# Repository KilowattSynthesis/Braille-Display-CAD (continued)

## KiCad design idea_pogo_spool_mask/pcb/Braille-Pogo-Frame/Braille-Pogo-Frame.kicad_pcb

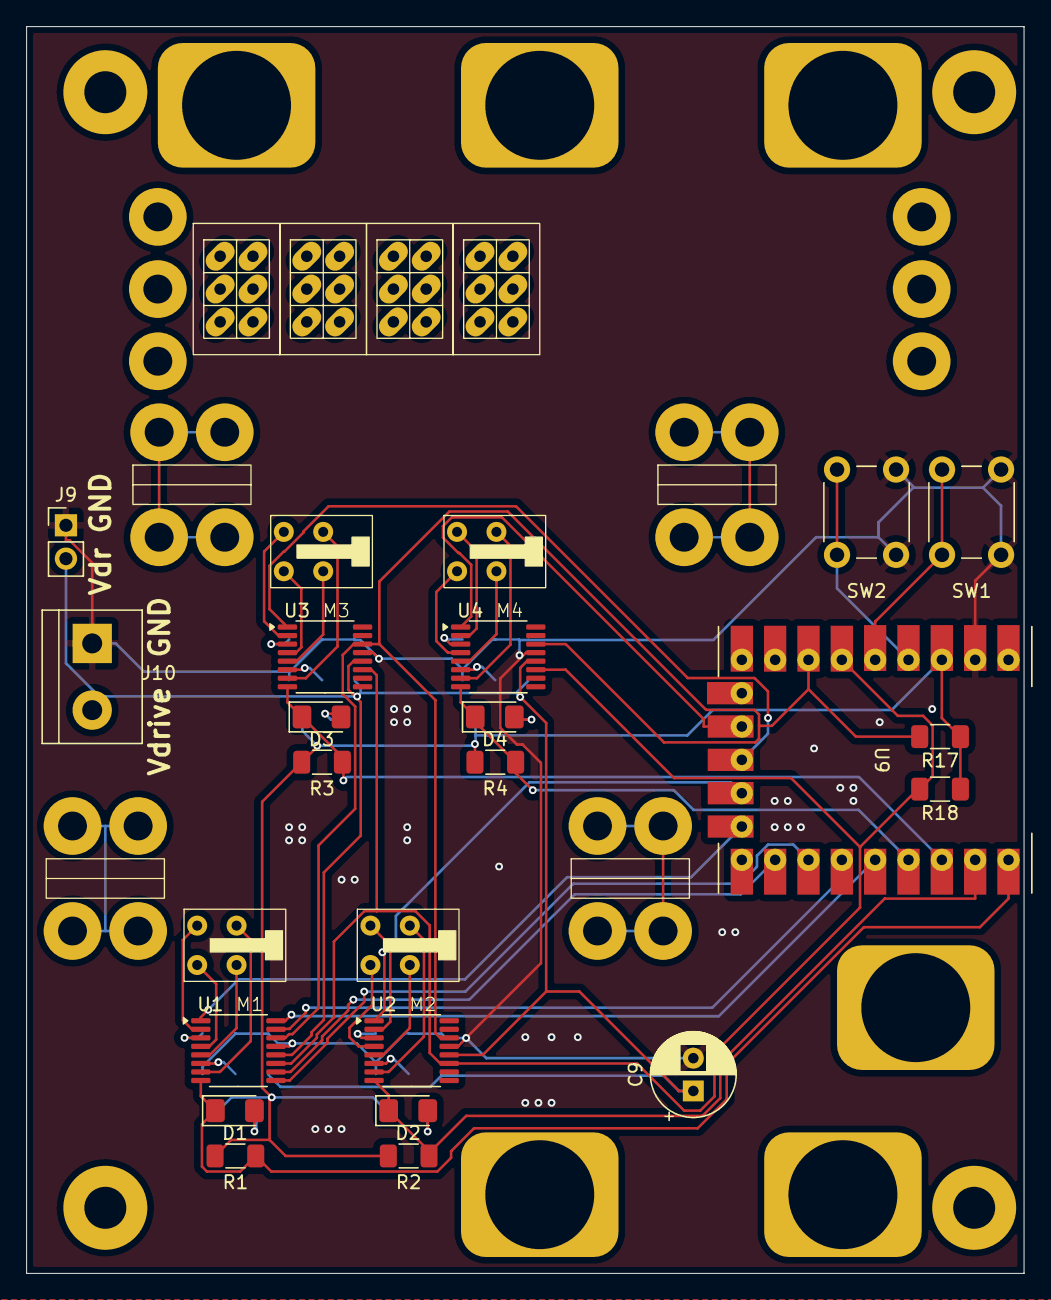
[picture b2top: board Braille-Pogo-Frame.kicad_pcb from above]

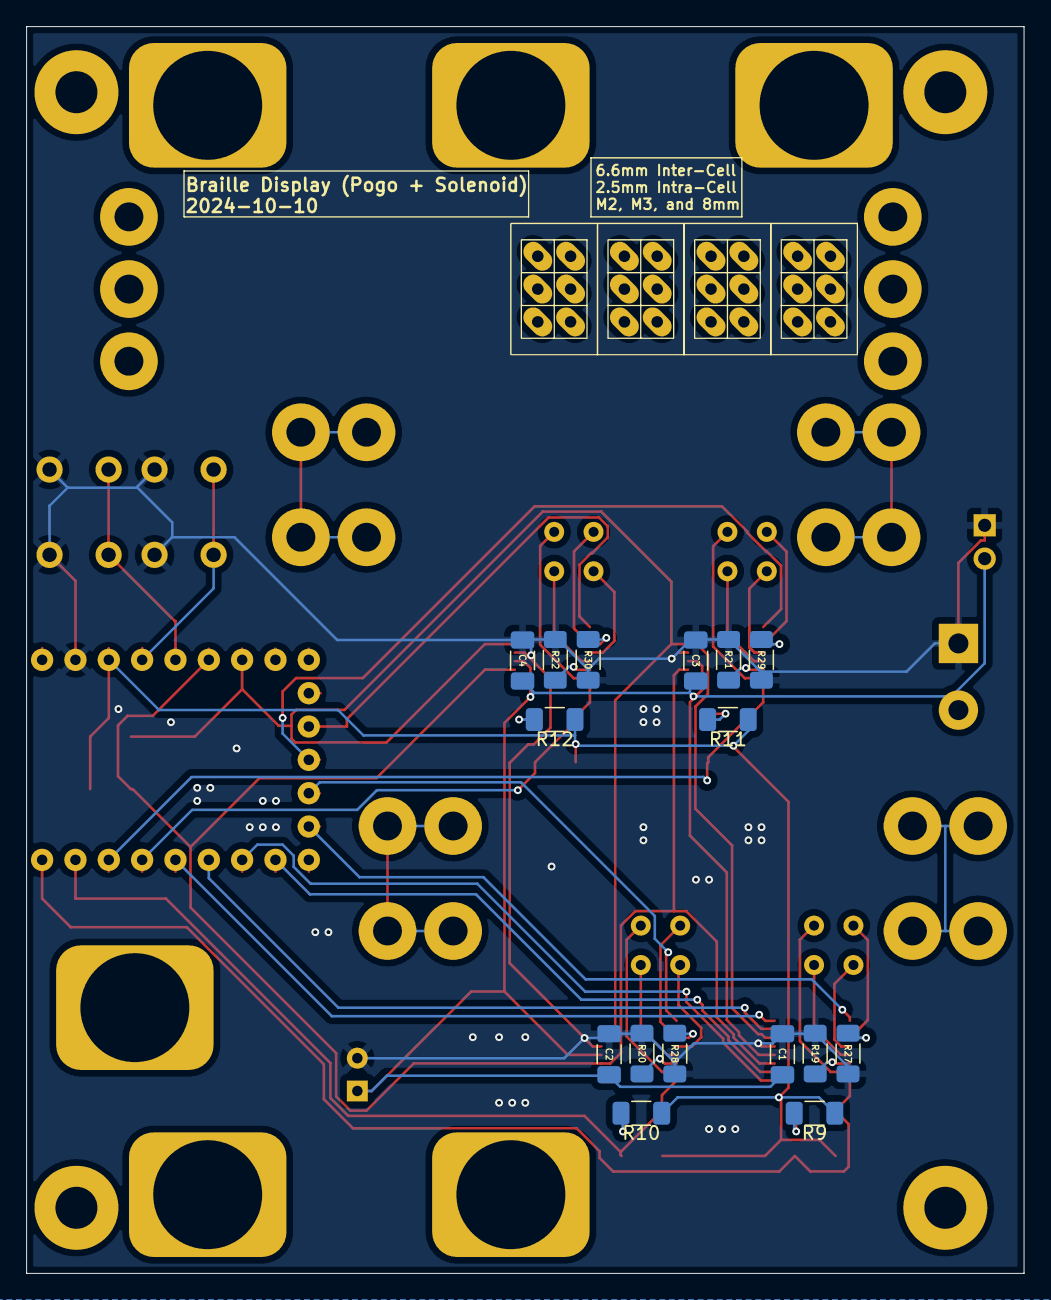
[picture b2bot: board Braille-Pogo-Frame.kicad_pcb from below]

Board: 2 copper layers, 76.0 x 95.0 mm, 64 parts (16 on the bottom side), 47 nets.

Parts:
C1, C2, C3, C4: 100n; C_1206_3216Metric_Pad1.33x1.80mm_HandSolder
C9: 10u; CP_Radial_D6.3mm_P2.50mm
D1, D2, D3, D4: LED; LED_1206_3216Metric_Pad1.42x1.75mm_HandSolder
H1, H2, H3, H4, H5, H6: MountingHole_Pad; MountingHole_8mm_Rect_NoSilk
H7, H8, H9, H10, H11, H12: MountingHole_Pad; MountingHole_2.2mm_M2_Pad_NoSilk
H13, H14, H15, H16: MountingHole_Pad; MountingHole_3.2mm_M3_Pad_NoSilk
H17, H18, H19, H20: MountingHole_Pad; HorizMounting_4x_M2_and_M3_Middle
J1, J2, J3, J4: Conn_01x06; Braille_Cell_Pogos_Solder_2.5mmIntra_6.6x10mmInter
J9: Conn_01x02; PinHeader_1x02_P2.54mm_Vertical
J10: Screw_Terminal_01x02; TerminalBlock_bornier-2_P5.08mm
M1, M2, M3, M4: Stepper_Motor_bipolar; MicroStepper_8mm-2mmGear
R1, R2, R3, R4, R17, R18: 5k1; R_1206_3216Metric_Pad1.30x1.75mm_HandSolder
R9, R10, R11, R12: 2k1; R_1206_3216Metric_Pad1.30x1.75mm_HandSolder
R19, R20, R21, R22, R27, R28, R29, R30: 330m; R_1206_3216Metric_Pad1.30x1.75mm_HandSolder
SW1, SW2: SW_Push; SW_PUSH_6mm
U1, U2, U3, U4: DRV8847SPWR; TSSOP-16_4.4x5mm_P0.65mm
U9: RP2040-Zero; RP2040 Zero

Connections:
+3V3: R1.1, R2.1, R3.1, R4.1, R9.1, R10.1, R11.1, R12.1, R17.1, R18.1, U9.3 (3V3)
/Braille_Cell1/~FAULT: D2.1 (K), R2.2, U2.8 (~FAULT), U9.11 (GP1)
/Braille_Cell1/~SLEEP: U2.1 (~SLEEP), U9.22 (GP10)
/Braille_Cell2/~FAULT: D3.1 (K), R3.2, U3.8 (~FAULT), U9.12 (GP2)
/Braille_Cell2/~SLEEP: U3.1 (~SLEEP), U9.21 (GP11)
/Braille_Cell3/~FAULT: D4.1 (K), R4.2, U4.8 (~FAULT), U9.13 (GP3)
/Braille_Cell3/~SLEEP: U4.1 (~SLEEP), U9.20 (GP12)
/Braille_Cell/IN1: U1.16 (IN1), U9.14 (GP4)
/Braille_Cell/IN2: U1.15 (IN2), U9.15 (GP5)
/Braille_Cell/IN3: U1.9 (IN3), U9.16 (GP6)
/Braille_Cell/IN4: U1.10 (IN4), U9.17 (GP7)
/Braille_Cell/~FAULT: D1.1 (K), R1.2, U1.8 (~FAULT), U9.10 (GP0)
/Braille_Cell/~SLEEP: U1.1 (~SLEEP), U9.23 (GP9)
GND: C1.2, C2.2, C3.2, C4.2, C9.2, J9.1, J10.1, R19.2, R20.2, R21.2, R22.2, R27.2, R28.2, R29.2, R30.2, SW1.1, SW2.1, U1.13 (GND), U2.13 (GND), U3.13 (GND), U4.13 (GND), U9.2 (GND)
I2C_SCL: R18.2, U1.11 (SCL), U2.11 (SCL), U3.11 (SCL), U4.11 (SCL), U9.6 (GP27)
I2C_SDA: R17.2, U1.14 (SDA), U2.14 (SDA), U3.14 (SDA), U4.14 (SDA), U9.7 (GP26)
unnamed: D1.2 (A), R9.2
unnamed: D2.2 (A), R10.2
unnamed: D3.2 (A), R11.2
unnamed: D4.2 (A), R12.2
unnamed: M1.2 (-), U1.4 (OUT2)
unnamed: M2.2 (-), U2.4 (OUT2)
unnamed: M3.2 (-), U3.4 (OUT2)
unnamed: M4.2 (-), U4.4 (OUT2)
unnamed: R27.1, U1.3 (ISEN12)
unnamed: R19.1, U1.6 (ISEN34)
unnamed: M1.1, U1.2 (OUT1)
unnamed: M1.3, U1.7 (OUT3)
unnamed: M1.4, U1.5 (OUT4)
unnamed: R28.1, U2.3 (ISEN12)
unnamed: R20.1, U2.6 (ISEN34)
unnamed: M2.1, U2.2 (OUT1)
unnamed: M2.3, U2.7 (OUT3)
unnamed: M2.4, U2.5 (OUT4)
unnamed: R29.1, U3.3 (ISEN12)
unnamed: R21.1, U3.6 (ISEN34)
unnamed: M3.1, U3.2 (OUT1)
unnamed: M3.3, U3.7 (OUT3)
unnamed: M3.4, U3.5 (OUT4)
unnamed: R30.1, U4.3 (ISEN12)
unnamed: R22.1, U4.6 (ISEN34)
unnamed: M4.1, U4.2 (OUT1)
unnamed: M4.3, U4.7 (OUT3)
unnamed: M4.4, U4.5 (OUT4)
unnamed: SW1.2, U9.5 (GP28)
unnamed: SW2.2, U9.4 (GP29)
Vdrive: C1.1, C2.1, C3.1, C4.1, C9.1, J9.2, J10.2, U1.12 (VM), U2.12 (VM), U3.12 (VM), U4.12 (VM)

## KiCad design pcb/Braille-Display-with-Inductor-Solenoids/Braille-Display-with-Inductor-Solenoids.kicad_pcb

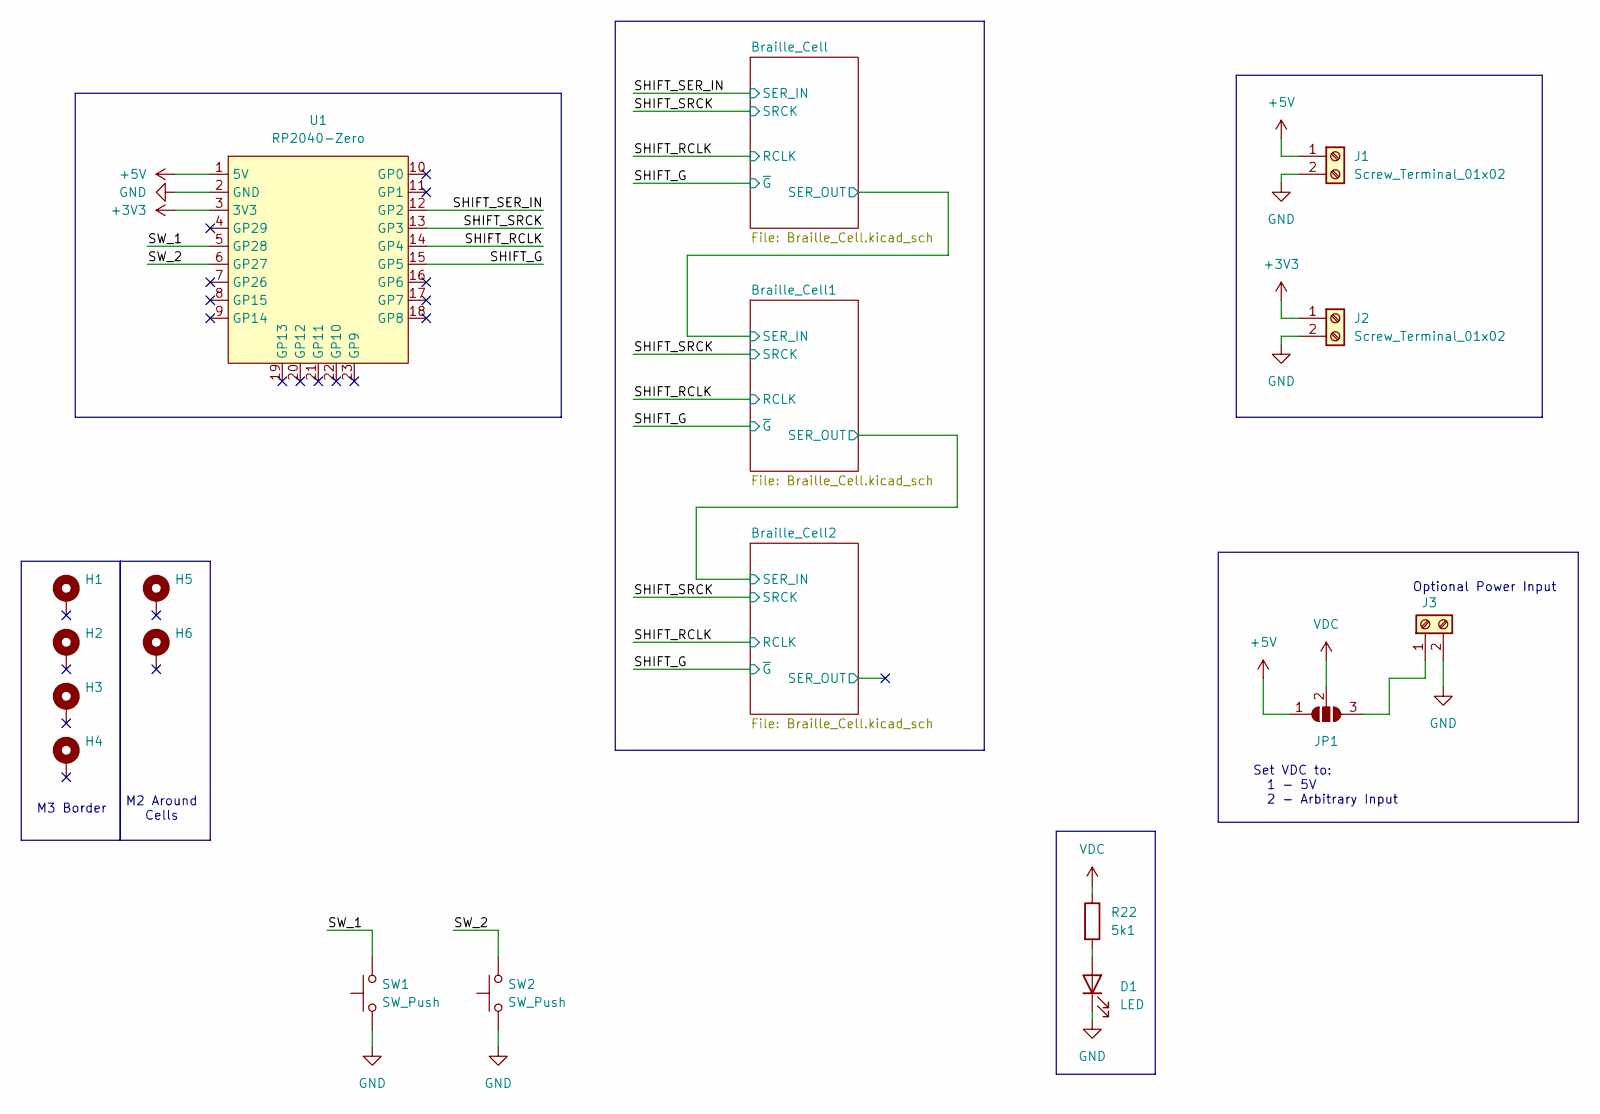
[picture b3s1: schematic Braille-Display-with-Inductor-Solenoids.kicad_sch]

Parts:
D1: LED; LED_1206_3216Metric_Pad1.42x1.75mm_HandSolder
H1, H2, H3, H4: MountingHole_Pad; MountingHole_3.2mm_M3_Pad
H5, H6: MountingHole_Pad; MountingHole_2.2mm_M2_Pad
J1, J2, J3: Screw_Terminal_01x02; TerminalBlock_bornier-2_P5.08mm
JP1: SolderJumper_3_Open; PinHeader_1x03_P2.54mm_Vertical
R22: 5k1; R_1206_3216Metric_Pad1.30x1.75mm_HandSolder
SW1, SW2: SW_Push; PushButtonSMD_2.93x3.9
U1: RP2040-Zero; RP2040 Zero

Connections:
+3V3: J2.1, U1.3 (3V3)
+5V: J1.1, JP1.1 (A), U1.1 (5V)
/SHIFT_G: U1.15 (GP5); also elsewhere on the board
/SHIFT_RCLK: U1.14 (GP4); also elsewhere on the board
/SHIFT_SER_IN: U1.12 (GP2); also elsewhere on the board
/SHIFT_SRCK: U1.13 (GP3); also elsewhere on the board
/SW_1: SW1.2, U1.5 (GP28)
/SW_2: SW2.2, U1.6 (GP27)
GND: D1.1 (K), J1.2, J2.2, J3.2, SW1.1, SW2.1, U1.2 (GND); also elsewhere on the board
unnamed: D1.2 (A), R22.2
unnamed: J3.1, JP1.3 (B)
VDC: JP1.2 (C), R22.1; also elsewhere on the board

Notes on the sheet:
M2 Around Cells
Optional Power Input
M3 Border
Set VDC to: 1 - 5V 2 - Arbitrary Input

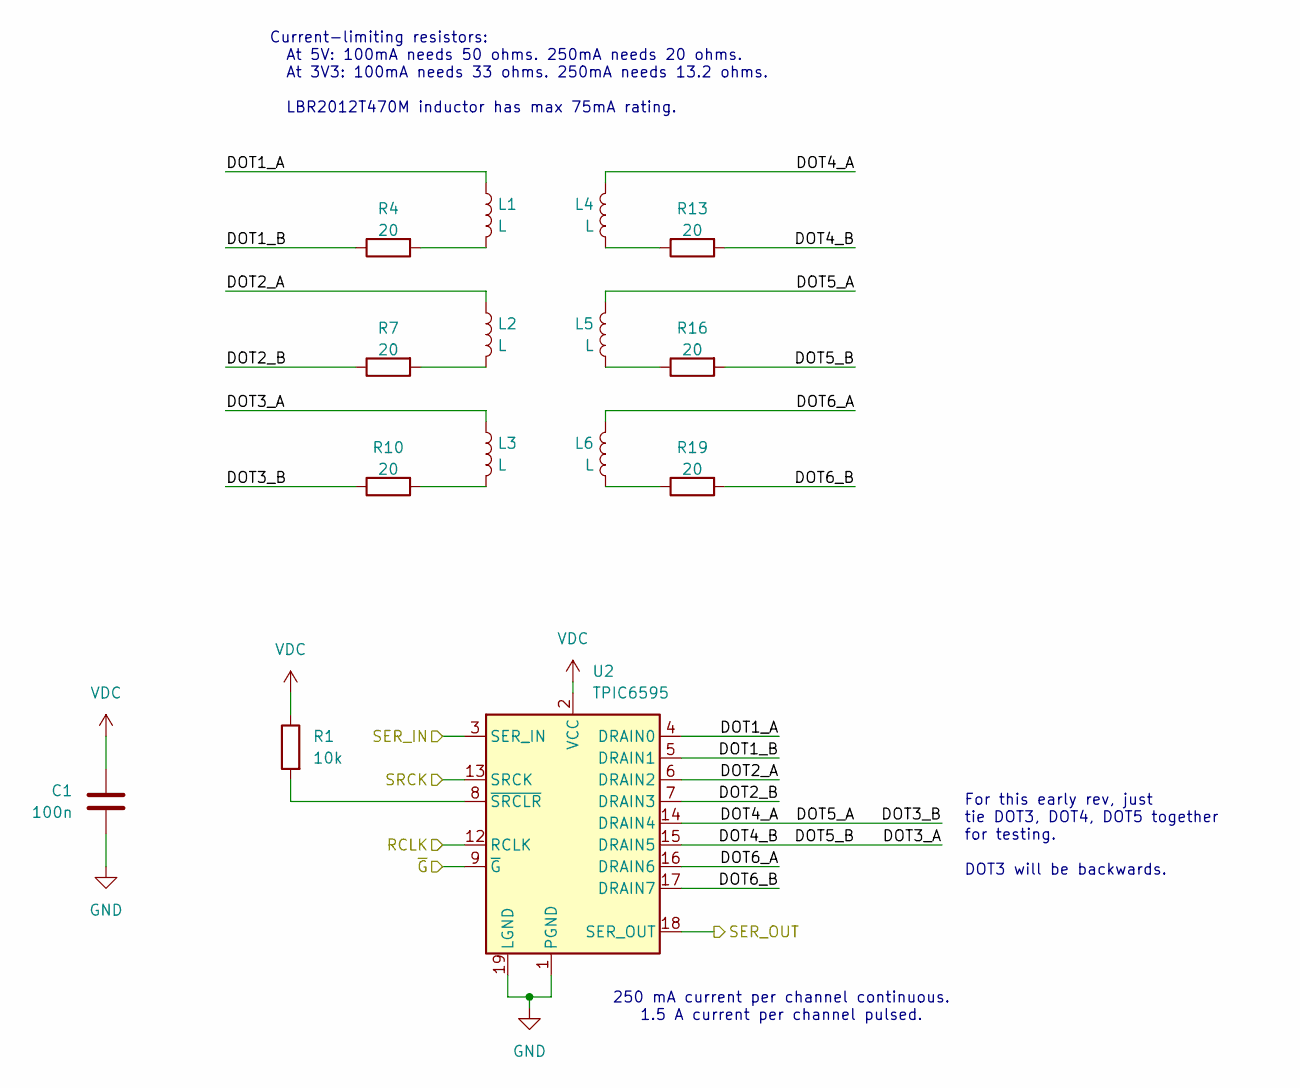
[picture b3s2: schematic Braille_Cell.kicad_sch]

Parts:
C1: 100n; C_0603_1608Metric
L1, L2, L3, L4, L5, L6: L; Inductor_0805_2012Metric_SMD_Vertical_Square
R1: 10k; C_0603_1608Metric_Pad1.08x0.95mm_HandSolder
R4, R7, R10, R13, R16, R19: 20; C_0603_1608Metric_Pad1.08x0.95mm_HandSolder
U2: TPIC6595; SOIC-20W_7.5x12.8mm_P1.27mm

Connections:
/Braille_Cell/DOT1_A: L1.1, U2.4 (DRAIN0)
/Braille_Cell/DOT1_B: R4.1, U2.5 (DRAIN1)
/Braille_Cell/DOT2_A: L2.1, U2.6 (DRAIN2)
/Braille_Cell/DOT2_B: R7.1, U2.7 (DRAIN3)
/Braille_Cell/DOT3_A: L3.1, R13.2, R16.2, U2.15 (DRAIN5)
/Braille_Cell/DOT3_B: L4.1, L5.1, R10.1, U2.14 (DRAIN4)
/Braille_Cell/DOT6_A: L6.1, U2.16 (DRAIN6)
/Braille_Cell/DOT6_B: R19.2, U2.17 (DRAIN7)
/Braille_Cell/SER_OUT: U2.18 (SER_OUT); also elsewhere on the board
/SHIFT_G: U2.9 (~G); also elsewhere on the board
/SHIFT_RCLK: U2.12 (RCLK); also elsewhere on the board
/SHIFT_SER_IN: U2.3 (SER_IN); also elsewhere on the board
/SHIFT_SRCK: U2.13 (SRCK); also elsewhere on the board
GND: C1.2, U2.1 (PGND), U2.10 (PGND), U2.11 (PGND), U2.19 (LGND), U2.20 (PGND); also elsewhere on the board
unnamed: L1.2, R4.2
unnamed: L2.2, R7.2
unnamed: L3.2, R10.2
unnamed: L4.2, R13.1
unnamed: L5.2, R16.1
unnamed: L6.2, R19.1
unnamed: R1.2, U2.8 (~SRCLR)
VDC: C1.1, R1.1, U2.2 (VCC); also elsewhere on the board

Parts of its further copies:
C2, C3: 100n; C_0603_1608Metric
L7, L8, L9, L10, L11, L12, L13, L14, L15, L16, L17, L18: L; Inductor_0805_2012Metric_SMD_Vertical_Square
R2, R3: 10k; C_0603_1608Metric_Pad1.08x0.95mm_HandSolder
R5, R6, R8, R9, R11, R12, R14, R15, R17, R18, R20, R21: 20; C_0603_1608Metric_Pad1.08x0.95mm_HandSolder
U3, U4: TPIC6595; SOIC-20W_7.5x12.8mm_P1.27mm

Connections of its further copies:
/Braille_Cell1/DOT1_A: L7.1, U3.4 (DRAIN0)
/Braille_Cell1/DOT1_B: R5.1, U3.5 (DRAIN1)
/Braille_Cell1/DOT2_A: L8.1, U3.6 (DRAIN2)
/Braille_Cell1/DOT2_B: R8.1, U3.7 (DRAIN3)
/Braille_Cell1/DOT3_A: L9.1, R14.2, R17.2, U3.15 (DRAIN5)
/Braille_Cell1/DOT3_B: L10.1, L11.1, R11.1, U3.14 (DRAIN4)
/Braille_Cell1/DOT6_A: L12.1, U3.16 (DRAIN6)
/Braille_Cell1/DOT6_B: R20.2, U3.17 (DRAIN7)
/Braille_Cell1/SER_OUT: U3.18 (SER_OUT), U4.3 (SER_IN)
/Braille_Cell2/DOT1_A: L13.1, U4.4 (DRAIN0)
/Braille_Cell2/DOT1_B: R6.1, U4.5 (DRAIN1)
/Braille_Cell2/DOT2_A: L14.1, U4.6 (DRAIN2)
/Braille_Cell2/DOT2_B: R9.1, U4.7 (DRAIN3)
/Braille_Cell2/DOT3_A: L15.1, R15.2, R18.2, U4.15 (DRAIN5)
/Braille_Cell2/DOT3_B: L16.1, L17.1, R12.1, U4.14 (DRAIN4)
/Braille_Cell2/DOT6_A: L18.1, U4.16 (DRAIN6)
/Braille_Cell2/DOT6_B: R21.2, U4.17 (DRAIN7)
/Braille_Cell2/SER_OUT: U4.18 (SER_OUT)
/Braille_Cell/SER_OUT: U3.3 (SER_IN); also elsewhere on the board
/SHIFT_G: U3.9 (~G), U4.9 (~G); also elsewhere on the board
/SHIFT_RCLK: U3.12 (RCLK), U4.12 (RCLK); also elsewhere on the board
/SHIFT_SRCK: U3.13 (SRCK), U4.13 (SRCK); also elsewhere on the board
GND: C2.2, C3.2, U3.1 (PGND), U3.10 (PGND), U3.11 (PGND), U3.19 (LGND), U3.20 (PGND), U4.1 (PGND), U4.10 (PGND), U4.11 (PGND), U4.19 (LGND), U4.20 (PGND); also elsewhere on the board
unnamed: L7.2, R5.2
unnamed: L8.2, R8.2
unnamed: L9.2, R11.2
unnamed: L10.2, R14.1
unnamed: L11.2, R17.1
unnamed: L12.2, R20.1
unnamed: L13.2, R6.2
unnamed: L14.2, R9.2
unnamed: L15.2, R12.2
unnamed: L16.2, R15.1
unnamed: L17.2, R18.1
unnamed: L18.2, R21.1
unnamed: R2.2, U3.8 (~SRCLR)
unnamed: R3.2, U4.8 (~SRCLR)
VDC: C2.1, C3.1, R2.1, R3.1, U3.2 (VCC), U4.2 (VCC); also elsewhere on the board

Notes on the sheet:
Current-limiting resistors: At 5V: 100mA needs 50 ohms. 250mA needs 20 ohms. At 3V3: 100mA needs 33 ohms. 250mA needs 13.2 ohms. LBR2012T470M inductor has max 75mA rating.
For this early rev, just tie DOT3, DOT4, DOT5 together for testing. DOT3 will be backwards.
250 mA current per channel continuous. 1.5 A current per channel pulsed.

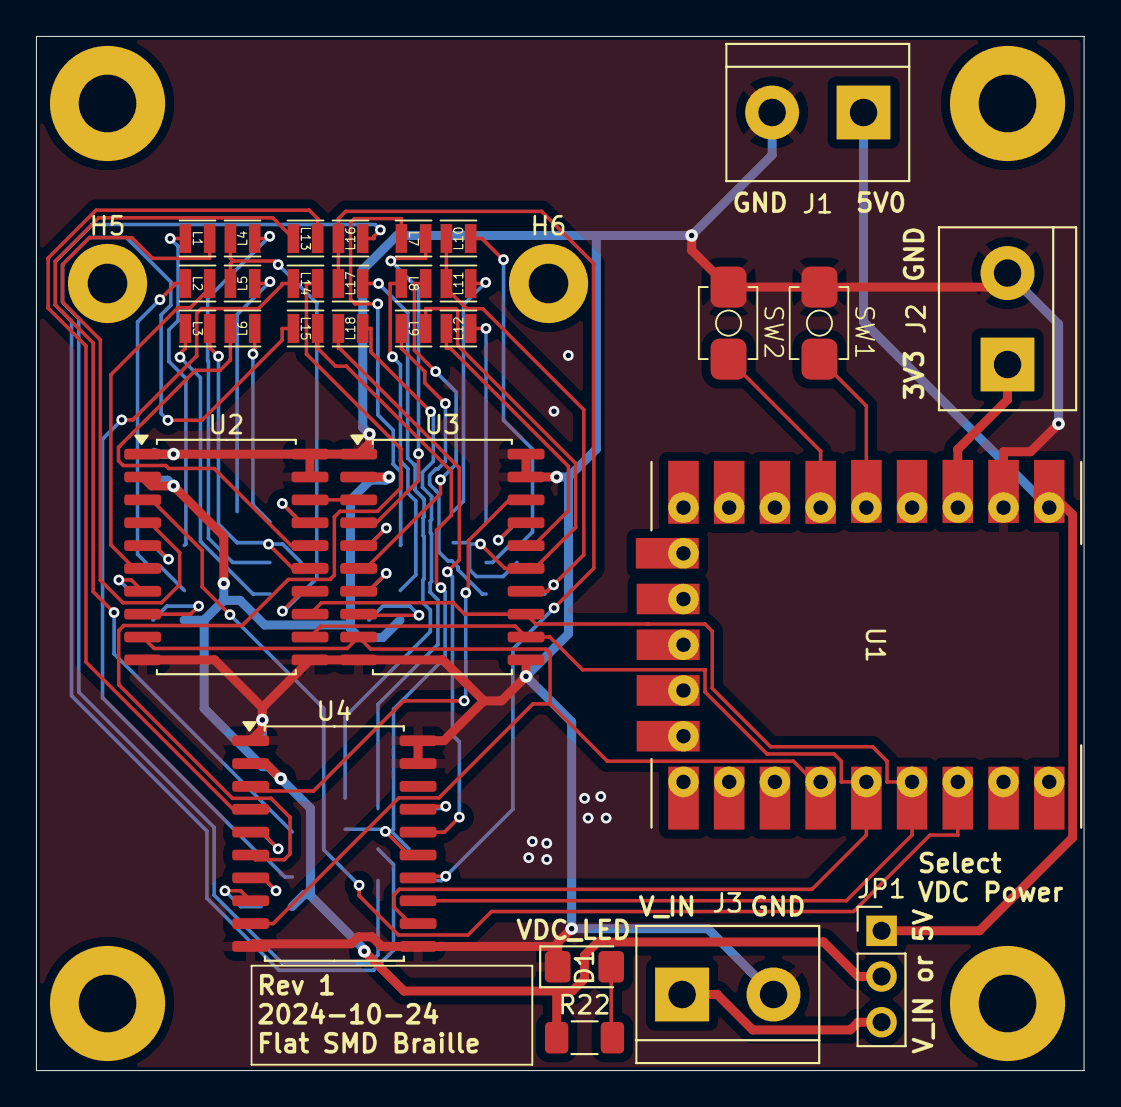
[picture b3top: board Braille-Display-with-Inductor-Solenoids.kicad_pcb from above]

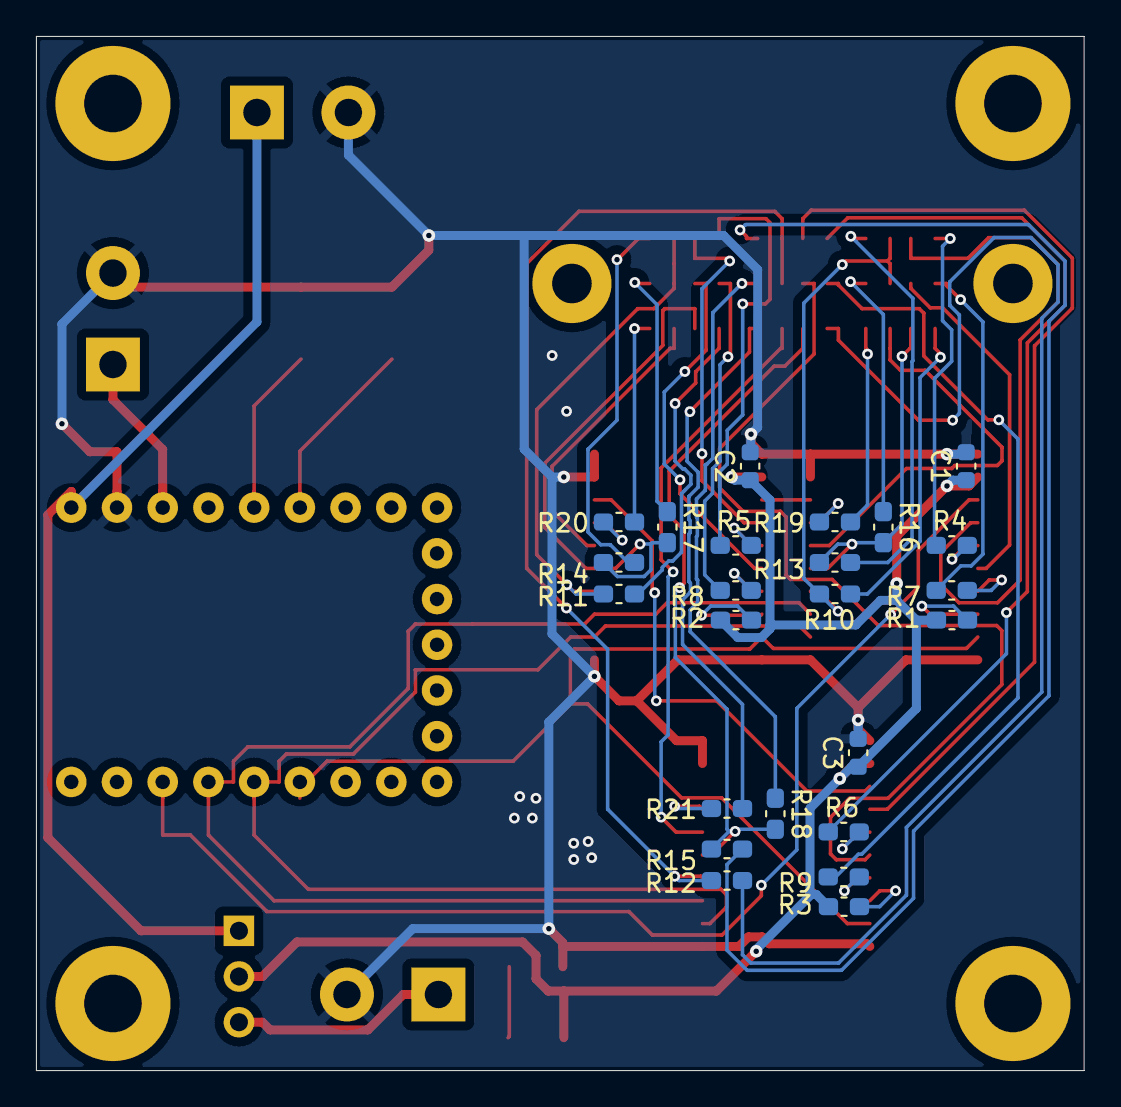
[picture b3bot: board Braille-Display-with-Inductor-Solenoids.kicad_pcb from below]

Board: 2 copper layers, 58.2 x 57.4 mm, 60 parts (24 on the bottom side), 59 nets.

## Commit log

2024-09-04 Rename files and add README parts
2024-09-05 Create housing and snorkel cable tubes
2024-09-05 Add cable guides through the roof
2024-09-05 Tweak dimensions for test print
2024-09-08 Variable name changes mostly
2024-09-08 Fix type checking config
2024-09-09 Clean up housing channels out bottom
2024-09-09 Clean up dead/demo code
2024-09-10 Create chain, enable ruff
2024-09-12 Create motor base POC
2024-10-06 Add ideas to README
2024-10-06 Add motor_base_1x part
2024-10-06 Add KiCAD to Gitignore
2024-10-06 Create pogo solder-side PCB (WIP)
2024-10-06 Move PCB down
2024-10-06 Refactor Braille Cells, add Stepper footprint
2024-10-06 Update microstepper pins
2024-10-06 Begin implementing blocker plate
2024-10-06 PCB: Add motors and motor driver to schematic
2024-10-06 PCB: Update footprint assignments
2024-10-09 PCB: Place motor drivers and horiz. rail mounts
2024-10-10 Create horizontal_bar_holder CAD
2024-10-11 Add horiz mounting standoffs, layout
2024-10-14 Purge motor_base design
2024-10-16 Create motor CAD model
2024-10-16 Create spool_motor_assembly
2024-10-21 Update stepper motor cad dimensions, PCB footprint mostly
2024-10-21 Create render of gear-based PCB in current state
2024-10-24 Add ideas with inductors
2024-10-24 Create PCB with vertical inductor layout
2024-10-24 Update net class rules for routing
2024-10-24 Finish up board
2024-10-24 Add Rev 1 production files
2024-10-24 Create flat inductor PCB
2024-10-24 Create rev1_flat production files
2024-10-24 Update to better bearing which fits within spool; simplify spool creation logic
2024-10-24 Update spool geometry so it fits
2024-10-24 Clean up layout and spacing
2024-10-24 Routing and finishing touches; ready to order
2024-10-25 Update/simplify housing for pogo pins
2024-10-25 Update ideas: CNC plotters, GT2 belt
2024-10-25 Add PDF schematic
2024-10-28 Add `build123d-ease` to requirements
2024-10-28 Improve scaling and output dir
2024-10-28 Create silicone sheet mold
2024-10-31 Update ideas, esp. for plotter idea/BOM
2024-10-31 Update branch names
2024-10-31 Create nut holder
2024-10-31 Add standoffs
2024-10-31 Dedent constructor with refactor
2024-10-31 Bump build123-ease version
2024-10-31 Set version more precisely
2024-10-31 Start making the rest of the plotter parts
2024-10-31 Lock in rev1 order (PCB and cad parts)
2024-11-05 Create helix examples
2024-11-05 Create ball screw versions
2024-11-05 Create viable ball screw implementation
2024-11-05 Lock in wavy screw design MVP
2024-11-05 Add grippers on ends
2024-11-05 Add failed attempt at cross-sectional area calc
2024-11-05 Bump build123d-ease version
2024-11-09 Clean up old experimentation
2024-11-09 WIP - Add curve logic updates, doesn't render
2024-11-10 Add gripper grooves
2024-11-11 Use suggested sweep mechanism with transition arg
2024-11-11 Bump requirements version to fix build
2024-11-13 WIP: Start housing
2024-11-20 Create start of housing
2024-11-20 Add holders for the ball screws
2024-11-20 Add channels where the screws are
2024-11-20 Add comment
2024-11-21 Add current sense comments to schematic
2024-11-21 Create motor demo firmware
2024-11-21 Simplify NeoPixel access in firmware
2024-11-21 Create solenoid base design - ordering
2024-11-22 Create separate spool
2024-11-23 Add winding adapter
2024-11-24 Try with new output diameter sizing
2024-12-01 Bump build123d_ease version
2024-12-01 Change output directory
2024-12-19 Bump bde version
2024-12-19 Create vertical motor demo
2024-12-19 Update note about 3mm motor pitch
2024-12-19 Linting fixes, bump versions
2024-12-19 Prepare to merge all idea branches
2024-12-19 Prepare to merge all idea branches (#1)
2024-12-19 Move stuff around
2024-12-19 Add "pogo spool mask" idea
2024-12-19 Limit CI to CAD only
2024-12-19 Update run restriction
2024-12-19 Update build output path
2024-12-19 Add "pogo spool mask" idea (#2)
2024-12-19 Update build path, prep for merge
2024-12-19 Fix for CI
2024-12-19 Add idea CAD - silicone sheet mold (#3)
2024-12-19 CAD - Solenoid Base Tubes and Coil Winding Adapter
2024-12-19 CAD - Solenoid Base Tubes and Coil Winding Adapter (#4)
2024-12-19 Create vertical motor layers demo
2024-12-19 Create vertical motor layers demo (#5)
2024-12-19 Add nut/bolt grid base CAD
2024-12-19 Add nut/bolt grid base CAD (#6)
2024-12-19 Fix CI
2024-12-19 Try forcing more runs
2024-12-19 Try even more runs
2024-12-19 Ball screw and housing CAD (#7)
2024-12-19 Add vertical and flat inductor PCBs (rev1)
2024-12-19 Add vertical and flat inductor PCBs (rev1) (#8)
2024-12-19 Attempt: Upload CAD build artifacts
2024-12-19 Decrease size of cad build
2024-12-19 Fix artifact path
2024-12-19 Update idea/construction log
2024-12-19 Upload CAD build artifacts after CI (#9)
2024-12-19 Update ruff rule
2024-12-19 Create magnetic cam POC
2024-12-19 Add 45-degree cams idea
2024-12-20 WIP: Dot column cam rod
2024-12-22 Add little divots
2024-12-22 nut_bolt_grid: Add M1p4 designs
2024-12-22 Motor driver demo firmware - Add `disable_motor` function, reverse direction, better config
2024-12-23 Show dots in vertical motor layers demo
2024-12-23 Prep vertical motor layers housing CAD
2024-12-23 Add top plate CAD for vertical motor layers design
2024-12-23 Add pre-tapped variant of top plate
2024-12-24 Re-optimize vertical motor layers for no thin walls
2024-12-24 Add vertical motor layers variant for FDM
2024-12-27 Ball screw - Add print-in-place prototype
2024-12-27 Add additional turner lengths to ball screw concept
2024-12-27 Create magnetic cam POC (#10)
2024-12-27 Create dot column cam design (#11)
    * WIP: Dot column cam rod
    * Add little divots
2024-12-27 Reorganize column-based rod designs
2024-12-28 Add fake_motor_chunk for testing vertical_motor_layers
2024-12-28 Style - use even spacing function from library now
2024-12-29 WIP: Create generic column rod assembly base
2024-12-29 Finish interface and slop design
2024-12-29 Create generic column rod housing design (#12)
2024-12-29 Rename cam rod design
2024-12-29 Create dot_column_cam_rod_octagon
2024-12-29 Create octagon cam housing demo
2024-12-29 Add gear to octagon cam housing unit
2025-01-01 Create column rod enclosure
2025-01-02 Create magnet aligner for inductor testing
2025-01-02 Column rod cad: Add zeroing magnets, motor mate
2025-01-02 PCB - Column rods - start with big progress
2025-01-02 Re-organize, create `demo_gggears_worm_gears.py` file
2025-01-06 Add explanation README for inductor magnets PCBs
2025-01-06 WIP: Rods PCB placement
2025-01-06 WIP: Place the housing and motor X
2025-01-06 WIP: Position everything
2025-01-06 WIP: Update tight placement of DC motor
2025-01-06 WIP: Layout and route the stepper driver
2025-01-06 WIP: Motor layout is good
2025-01-06 WIP: Manual routing and silkscreens
2025-01-06 Comments
2025-01-06 Big routing
2025-01-06 Clean up DRC (mostly footprints)
2025-01-06 Fix spacing issue on top
2025-01-06 Fix spacing issues on bottom
2025-01-06 Create render of 6mm motor, add to PCB
2025-01-06 WIP: Get cams good
2025-01-06 WIP: Reorder the cam bushing and hall sensor
2025-01-06 Finish and tag release
2025-01-06 Complete type 4 rev 1
2025-01-06 Create dc_motor_clamp cad
2025-01-06 Create PCB and CAD for Type 4 Rev 1 rod cams (#13)
    * WIP: Rods PCB placement
    * WIP: Place the housing and motor X
    * WIP: Position everything
    * WIP: Update tight placement of DC motor
    * WIP: Layout and route the stepper driver
    * WIP: Motor layout is good
2025-01-09 Vertical motor layers: Add slice for one-layer-per-PCB assembly
2025-01-10 Rename migrated script
2025-01-11 Move/rename folders to mark as migrated
2025-02-03 Update column rods design
2025-02-03 Pin bad dependency
2025-06-30 Mark Column Rods design as migrated to separate repo
